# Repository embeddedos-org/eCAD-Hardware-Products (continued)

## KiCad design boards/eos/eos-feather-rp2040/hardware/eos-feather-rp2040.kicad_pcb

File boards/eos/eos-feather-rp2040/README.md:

# EoS Feather RP2040

An original RP2040 board in the Feather form factor, 50.8 × 22.86 mm, four layers.
Designed by Kartikeydheer Srivastava.
All rights reserved: not open source, and not under this repository's MIT licence.
Anyone may view it, clone this repository and run its tests; anything more needs
Kartikeydheer Srivastava's written permission (kartikeydheer@gmail.com). EmbeddedOS (EoS) Research Foundation has a limited, revocable
permission. See [LICENSE.txt](LICENSE.txt) and [the licence summary](../README.md#licence).

A board for the same job as Adafruit's Feather RP2040 (product 4884); an original design, not a
copy: no design file of the vendor's was used (no schematic, layout, CAD, Gerber or BOM). The
outline, hole and header positions come from Adafruit's
[Feather Specification](https://learn.adafruit.com/adafruit-feather/feather-specification) (its
text and dimension drawing), and the signal on each header pin, the user button's GPIO and the
battery polarity from Adafruit's published
[Feather RP2040 pinout](https://learn.adafruit.com/adafruit-feather-rp2040-pico/pinouts) and
its pinout diagram. "Feather" is used only to say what the board fits; it is not an Adafruit
product.

| | |
|---|---|
|  |  |

FeatherWings, and CircuitPython or Arduino code written for the Feather RP2040's pinout, find the
same signals on the same pins. The flash is 16 MB, not 8 MB: firmware built for the Feather
RP2040 runs from its first 8 MB.

## What is on it

| Block | Parts, values and source |
|---|---|
| Outline, holes, headers | 0.9 × 2.0 in with 0.1 in holes at each corner, their centres 0.1 in from each edge. A 16-pin strip along the bottom edge centred 1.0 in from the left edge, a 12-pin strip along the top edge 1.2 in from the left, 0.8 in apart; pin order from the USB end. Source: Adafruit [Feather Specification](https://learn.adafruit.com/adafruit-feather/feather-specification) (text and dimension drawing), as EoS Motion Wing uses it. Holes: KiCad's 2.5 mm unplated hole, the nearest stock size to 0.1 in; corner radius 2.54 mm, concentric with the holes (the spec gives none). Male headers on the back (Würth 61301611121, 61301211121): pins point down, for a breadboard or a Feather socket. |
| MCU | Raspberry Pi RP2040, QFN-56 7 × 7 mm; its single ground is the centre pad (RP2040 datasheet Table 1), which has a 2 × 2 array of vias into the ground plane. 100 nF at each IOVDD and DVDD pin and at USB_VDD and ADC_AVDD (datasheet 2.9.1–2.9.5); 1 µF at VREG_VIN and at VREG_VOUT, which feeds the DVDD pins (datasheet 2.10.1; [Hardware design with RP2040](https://datasheets.raspberrypi.com/rp2040/hardware-design-with-rp2040.pdf) 2.1.3); TESTEN to ground (Table 1). [RP2040 datasheet](https://datasheets.raspberrypi.com/rp2040/rp2040-datasheet.pdf), build 2025-02-20. |
| Crystal | Abracon ABM8-272-T3, 12 MHz, CL 10 pF, ESR 50 Ω, the crystal Raspberry Pi recommends; 15 pF C0G load capacitors and 1 kΩ in series with XOUT, tuned for IOVDD = 3.3 V (Hardware design with RP2040, 2.3 and Table 1). |
| Flash | Winbond W25Q128JVPIQ, 16 MB QSPI, WSON-8 6 × 5 mm: the guide's W25Q128JV (2.2) in its smaller package. 100 nF (C22) beside it, joined to VCC only through the 3.3 V plane (see [Layout](#layout)). Its exposed pad is left unconnected, with no via under it, as the [W25Q128JV data sheet](https://www.winbond.com/resource-files/w25q128jv%20revf%2003272018%20plus.pdf) Rev. F (section 10.3) asks. |
| BOOTSEL | 1 kΩ from QSPI_SS to the BOOT button, so QSPI_SS can over-drive the button when the chip boots; the 10 kΩ QSPI_SS pull-up (R7) is drawn but not fitted, as the guide does for this flash (2.2). |
| USB | HRO TYPE-C-31-M-12 as a 5 V sink: 5.1 kΩ Rd on CC1 and CC2 ([USB Type-C specification](https://www.usb.org/usb-type-cr-cable-and-connector-specification)). Littelfuse SP0503BAHTG on D+, D− and VBUS: diodes to ground only ([SP05xxBA data sheet](https://www.littelfuse.com/~/media/electronics/datasheets/tvs_diode_arrays/littelfuse_tvs_diode_array_sp05_datasheet.pdf.pdf)). 27 Ω in series with USB_DP and USB_DM, at the chip (RP2040 datasheet Table 1; guide 2.4.1). Littelfuse 0805L050WR polyfuse, 0.50 A hold, 1.00 A trip, 6 V, R1max 0.85 Ω (0805L data sheet, revised 10/29/21). |
| LiPo charger | Microchip MCP73831T-2ACI/OT, 4.20 V. R10 = 4.7 kΩ sets 1000 V / 4.7 kΩ = 213 mA (equation 5-1), inside the Feather spec's 100–500 mA. 10 µF on VDD and on VBAT, where the data sheet asks for at least 4.7 µF (sections 3.1, 3.2, 6.1.1.4). Yellow CHG LED from VBUS through 1 kΩ into STAT: lit while charging. [MCP73831 data sheet](https://ww1.microchip.com/downloads/aemDocuments/documents/APID/ProductDocuments/DataSheets/MCP73831-Family-Data-Sheet-DS20001984H.pdf) DS20001984H. |
| Battery and power path | JST PH 2-pin (S2B-PH-SM4-TB), the connector the Feather spec requires, polarity as Adafruit's cells (see [Battery polarity](#battery-polarity)). Load sharing as Microchip [AN1149](https://ww1.microchip.com/downloads/en/AppNotes/01149c.pdf) (DS01149C) Figures 5–7: an AOS AO3401A P-MOSFET from the battery to the system rail, its gate on USB power with a pull-down, and a Nexperia PMEG6010CEH Schottky from USB to the system rail. With USB present the MOSFET is off and USB runs the board while the charger charges the battery; without USB the pull-down turns it on. AO3401A Rev 3.1: RDS(on) ≤ 85 mΩ at VGS = −2.5 V. PMEG6010CEH v.4: VF ≤ 530 mV at 500 mA. The pull-down is 10 kΩ, not AN1149's 100 kΩ: see [Gate pull-down](#gate-pull-down). The battery line passes a 1 mm test pad, TP1, in the top-right corner. |
| 3.3 V | Diodes AP2112K-3.3TRG1, 600 mA, the regulator the Feather spec names; dropout ≤ 400 mV at 600 mA; stable with 1.0 µF ceramic capacitors (X5R/X7R); 10 µF X5R fitted at input and output. The Feather EN pin pulls its EN low; 100 kΩ to the system rail holds it high otherwise (EN high above 1.5 V; 3 MΩ internal pull-down). [AP2112 data sheet](https://www.diodes.com/assets/Datasheets/AP2112.pdf) DS39724 Rev. 2-2. |
| Buttons | RESET (RUN, which has an internal pull-up: RP2040 datasheet Table 619), BOOT and USER, Omron B3U-1000P (A162-E1-07), along the bottom right: RST, USR, BOOT from left to right. USER is on GPIO4, where Adafruit's pinout puts the Feather RP2040's user-readable button; turn on GPIO4's internal pull-up in firmware (the pins reset with pull-downs, datasheet Table 615). |
| LEDs | Red user LED on D13 (GPIO13), Kingbright APTD1608LSURCK through 1 kΩ: 1.55 mA at VF 1.75 V (DSAO7433), under the pin's 4 mA default drive. Yellow CHG LED, APTD1608LSYCK (DSAO7434). The spec asks for the user LED above the USB connector and suggests the CHG LED below it; both are there. |
| SWD | Raspberry Pi 3-pin debug connector, JST SH BM03B-SRSS-TB: 1 SWCLK, 2 GND, 3 SWDIO ([RP-003139-SP-4](https://datasheets.raspberrypi.com/debug/debug-connector-specification.pdf)), marked SWD. It takes a Raspberry Pi Debug Probe's cable. The specification recommends 100 Ω in series at the target's pins "unless the platform is very low cost and/or space constrained"; there is no room for them beside the RP2040's pins 20–26 (XIN, XOUT, DVDD, SWCLK, SWDIO and RUN at 0.4 mm pitch, with R5 and C20 in front of them), so they are left out. |
| STEMMA QT / Qwiic | JST SH SM04B-SRSS-TB on SDA/SCL (GPIO2/GPIO3, I2C1), 1 GND, 2 3.3 V, 3 SDA, 4 SCL ([STEMMA QT technical specs](https://learn.adafruit.com/introducing-adafruit-stemma-qt/technical-specs), the Qwiic convention). No pull-ups on the board: the spec puts them on the I2C devices and on the wings. |

### Feather pins

| Pin | Header | Signal | | Pin | Header | Signal |
|---|---|---|---|---|---|---|
| RST | 16-pin, 1 | RUN | | BAT | 12-pin, 1 | battery + |
| 3V | 16-pin, 2 | 3.3 V | | EN | 12-pin, 2 | regulator enable |
| 3V | 16-pin, 3 | 3.3 V (AREF in the spec; see below) | | USB | 12-pin, 3 | USB 5 V, after the polyfuse |
| GND | 16-pin, 4 | ground | | D13 | 12-pin, 4 | GPIO13, red LED |
| A0–A3 | 16-pin, 5–8 | GPIO26–GPIO29 (ADC0–ADC3) | | D12, D11, D10, D9 | 12-pin, 5–8 | GPIO12, GPIO11, GPIO10, GPIO9 |
| D24, D25 | 16-pin, 9–10 | GPIO24, GPIO25 | | D6, D5 | 12-pin, 9–10 | GPIO8, GPIO7 |
| SCK, MO, MI | 16-pin, 11–13 | GPIO18, GPIO19, GPIO20 (SPI0) | | SCL, SDA | 12-pin, 11–12 | GPIO3, GPIO2 (I2C1), and the STEMMA QT |
| RX, TX | 16-pin, 14–15 | GPIO1, GPIO0 (UART0) | | | | |
| D4 | 16-pin, 16 | GPIO6 | | | | |

GPIO4 is the USER button. GPIO5, GPIO14–17 and GPIO21–23 are not connected. The spec's AREF
position (16-pin, 3) carries 3.3 V, as on Adafruit's pinout: the RP2040 has no separate ADC
reference pin, and the spec says to leave AREF unconnected on such a chip, so a wing that drives
an analog reference into that pin would meet this board's 3.3 V rail.

### Gate pull-down

On battery, D1 is reverse-biased by the system rail and its leakage flows into Q1's gate node,
whose only path to ground is the pull-down. The gate rises by the leakage times the pull-down.
With AN1149's 100 kΩ and a very-low-VF Schottky (onsemi's MBR120VL is allowed 0.6 mA at 25 °C),
the gate could reach the system rail and turn Q1 off. PMEG6010CEH (v.4) leaks 0.8 µA typical at
5 V and at most 50 µA at 60 V (25 °C); its Fig. 2 shows about 65 µA at 5 V and 85 °C (typical;
the data sheet gives no maximum above 25 °C). Through 10 kΩ that lifts the gate at most 0.5 V at
25 °C and about 0.65 V at 85 °C, so VGS stays below −2.3 V down to a 3.0 V cell, past the
AO3401A's −1.3 V maximum threshold. With USB present the pull-down takes 0.5 mA.

### Battery polarity

Adafruit's pinout diagram marks the battery connector: − toward the USB end and + away from it,
on a connector that faces the 12-pin edge. Looking into that connector from outside the board,
top side up, + is on the left. This board's connector faces the right-hand edge and keeps that
convention: looking into it, + (J4 pin 1) is on the left, toward the 16-pin edge. The marks
+ and − are on the silkscreen beside it. Cells from other makers may be wired the other way
round; check a cell with a meter before plugging it in.

## Not on this board

- **NeoPixel.** The Feather RP2040 has an RGB NeoPixel on GPIO16; this board has none, and
  GPIO16 is not connected.
- **The 2 × 5 1.27 mm SWD footprint and the bottom SWD pads.** The Raspberry Pi 3-pin connector
  replaces them.
- **The battery connector's position.** The Feather spec says the JST PH "must" be 0.425 in
  from the left edge, on the 12-pin edge beside the USB connector. With KiCad's stock footprints,
  the courtyards of the HRO TYPE-C-31-M-12 (10.6 mm wide, extended by its rear shell tabs) and of
  the S2B-PH-SM4-TB (10.2 mm deep) overlap at that spot, so the connector is at the right-hand end,
  facing out of it. A USB-C receptacle with a shorter rear, or a mid-mount one, might allow the
  spec position. This is a deviation from a "must" of the spec, awaiting the owner's decision. A
  case or a cable routing that expects the battery lead at the USB end will not fit.
- **USB at the exact centre of the left edge.** The receptacle is centred at y 11.90 mm, 0.47 mm
  below the edge's centre (11.43 mm), where the Feather spec puts USB; an enclosure's plug window
  centred on the edge has 0.47 mm less margin on one side.
- **Header pin labels.** Neither silkscreen labels the header pins; the
  [Feather pins](#feather-pins) table is the key.
- **Battery voltage monitor.** None, as on the Feather RP2040 (Adafruit's power page: no ADC is
  connected to a battery monitor).

## Layout

Measured from the routed board file, `hardware/eos-feather-rp2040.kicad_pcb`.

- **Crystal.** XIN runs 8.4 mm from pin 20 to the crystal and C23; XOUT 2.6 mm from pin 21 to
  R5, then 2.2 mm from R5 to the crystal and C24. All three are on the top layer with no via. On
  the bottom layer under the crystal, C23, C24, R5 and these lines the only track or via of another
  net is one ground via; the bottom ground pour covers the area. Next to the clock tracks, the
  nearest other tracks are those of the chip's neighbouring pins (3.3 V and ground), 0.24 mm away
  at the pad row, and the +1V1 line to C20, 0.55 mm away.
- **USB D+ near the crystal.** On its way from the ESD part to its via under the chip, D+ runs on
  the top layer through the crystal group: 0.17 mm from the crystal's ground pad (Y1.2), 0.18 mm
  from C24's ground pad (C24.2), 0.59 mm from C24's XTAL_OUT pad (C24.1) and 0.88 mm from the
  XTAL_OUT track, edge to edge. It crosses no clock line, and the ground plane (In1) under it there
  is solid. Rev B moves it out of the group (see [Rev B follow-ups](#rev-b-follow-ups)).
- **USB.** From the receptacle through the ESD part to R3 and R4: D+ 36.3 mm with 4 vias (two of
  them join the receptacle's A6 and B6 contacts), D− 35.1 mm with 2 vias, 0.2 mm wide. They are
  not a coupled pair: D+ runs 21.4 mm on the top layer and 14.9 mm on the bottom, D− 7.4 mm on the
  top and 27.7 mm on the bottom. Under the chip both are on the bottom layer, 0.5 to 1.4 mm apart
  centre to centre. From R3 and R4 to pins 47 and 46: 3.9 and 4.1 mm on the top layer.
- **QSPI.** SCLK 4.4 mm, SD0 2.9 mm, SD1 11.5 mm, SD2 9.0 mm, SD3 5.8 mm, all on the top layer
  with no via. SS runs 11.9 mm on the top layer from pin 56 to the flash's CS pad. From there a
  branch goes on to the BOOTSEL resistors right of the flash: 8.21 mm to R6 and 9.45 mm to R7
  (7.61 mm on the top layer, 1.84 mm on the bottom, 2 vias), where Hardware design with RP2040
  (2.2) asks for both resistors close to the flash. Rev B routes it directly.
- **Core supply (+1V1).** Each pin has a top-layer track to its capacitor: VREG_VOUT (pin 45) to
  C11 2.5 mm, DVDD pin 50 to C21 2.3 mm, DVDD pin 23 to C20 3.2 mm. One 0.2 mm line joins them:
  from C11 round the end of the USB D+ line beside R3, then on the bottom layer under the chip to
  C20, with a via down to it from pin 50's track; 32.6 mm of +1V1 track in all, 3 vias.
- **3.3 V decoupling, supply side.** Track length along the centrelines, pad centre to via
  centre. Each 3.3 V pin of the RP2040 has its own via inside the pad ring: 0.86 mm from pins 1,
  10, 22, 33, 42 and 48, 1.46 mm from pins 43 and 49, 2.06 mm from pin 44 (VREG_VIN); pin 43's
  track also passes over pin 42's via. C15 sits 1.2 mm from pin 33 on a direct top-layer track and
  uses pin 33's via. C12, C13, C14 and C16 have a via each (0.73 to 0.74 mm). C10 and C18 share
  one (C18 0.73 mm; C10 1.73 mm, through C18's pad). C17, C19 and C22 share another (C19 0.73 mm,
  C17 2.64 mm, C22 5.36 mm through C17's pad). Capacitor pad to pin pad: C16 1.4 mm (pin 42), C10
  3.3 mm (VREG_VIN, pin 44), C13 4.5 mm (pin 10), C18 5.0 mm (USB_VDD, pin 48), C19 5.1 mm
  (ADC_AVDD, pin 43), C17 6.5 mm (pin 49), C14 7.5 mm (pin 22), C12 8.2 mm (pin 1).
- **Decoupling, ground side.** Copper path from the pad's edge to the nearest ground via: C21's
  ground pad (DVDD pin 50) has the longest of any decoupling capacitor, 3.38 mm of top copper, to
  a via that C17 (1.93 mm) and C22 (0.33 mm) also use.
- **Flash decoupling.** C22, the flash's 100 nF, has no track to the flash's VCC pin (U2.8): it
  is turned with its ground pad between U2.8 and its 3.3 V pad. It reaches U2.8 only through the
  3.3 V plane: from C22's 3.3 V pad, 4.55 mm of copper (5.36 mm along the track centrelines) to
  the via it shares with C17 and C19, and that via is 6.73 mm from U2.8's own via. Hardware
  design with RP2040 (Figure 11) puts the 100 nF at the flash's VCC. Rev B turns C22 and routes
  it to U2.8, and moves C12, C14 and C17 nearer their pins.
- **Lines to the bottom right.** GPIO0 (TX), GPIO1 (RX), GPIO6 (D4) and GPIO4 (user button)
  leave the chip's top edge and change to the bottom layer above it. They run under the flash to
  the 16-pin strip and the button: 22.2, 22.3, 26.7 and 20.1 mm, with one or two vias each.
- **Battery line.** VBAT, 0.3 mm wide (0.225 mm where it enters the charger's pin), runs from
  J4 past TP1 and along the top edge, under the 12-pin strip, to the BAT pin and on to the
  charger: 63.3 mm with 3 vias.
- **Ground.** Ground is poured on both outer layers, with 39 ground vias. Every fragment of the
  outer-layer ground pours contains a ground via or a plated-through ground pin.

## Build results

The numbers below are from `build-report.json` and `drc.json` in this folder.

| Check | Result |
|---|---|
| Schematic ERC | 0 violations |
| DRC errors | 0 |
| Unconnected items | 0 |
| Schematic ↔ board parity | 0 differences |
| DRC warnings | 7: silkscreen within the board-edge clearance: the front outline of J1 (USB-C) at the left edge (2), and the back outlines of J2 (Feather 16-pin) and J3 (Feather 12-pin) at the bottom and top edges (2 and 3) |

## Fabrication

Four layers, 1.6 mm FR-4: signal, ground plane, 3.3 V plane, signal, with ground poured on both
outer layers. Measured from the board file:

- **Tracks:** 0.127 mm for signals; 0.2 mm for USB and +1V1, which enter the RP2040's
  0.4 mm-pitch pads; 0.2 and 0.3 mm for +3V3; 0.3 mm for VBUS, the battery and the system rail;
  ground tracks 0.127, 0.2 and 0.3 mm. Narrower where a track enters a fine-pitch pad: 0.095 mm
  on the USB-C receptacle's CC contacts, 0.225 mm on VBUS and VBAT at the receptacle and the
  charger, and one 0.15 mm segment on +3V3.
- **Clearance:** 0.127 mm; 0.15 mm around the USB, supply and power lines (their net classes).
- **Vias:** 0.45 mm with a 0.2 mm drill (109 vias).
- **Smallest drill:** 0.2 mm, in the vias.
- **Plated slots:** the USB-C receptacle's four shell holes are plated oval slots, 0.6 × 1.2 mm and
  0.6 × 1.7 mm (two of each): tell the fab the board has plated slots. Its two 0.65 mm peg holes
  are unplated.

The four vias in the RP2040's centre pad sit in its paste openings: order them filled and capped
(or plugged), so solder does not wick down them.

## What has not been done

- **No board has been made or tested.** These are design files that pass KiCad's electrical and
  design rule checks; no hardware has been built, powered, charged from or flashed.
- **No signal-integrity, thermal or charging test.** USB, QSPI and the crystal were not simulated
  or measured. The charger's thermal regulation and the AP2112K's temperature at full load were
  not measured.
- **Regulator heat.** The AP2112K's SOT-25 package is rated 184 °C/W (no heatsink). From USB the
  system rail is about 4.3–4.5 V, so 500 mA from the 3.3 V rail dissipates about 0.55 W, a rise of
  about 100 °C: the 500 mA is a peak, not a continuous load.
- **Charger heat.** The MCP73831 (230 °C/W, 4-layer JEDEC board) dissipates about 0.3 W at 213 mA
  from 5 V into a 3.6 V cell. The worst case is at the start of constant-current charging, where
  the cell is at the precondition threshold, 66.5 % of 4.20 V = 2.79 V (DS20001984H, VPTH/VREG):
  (5 − 2.79) V × 0.213 A = about 0.47 W, a rise of about 108 °C, so the charger's thermal
  regulation will cut the current there.
- **USB budget.** The polyfuse holds 0.50 A at 20 °C, and less when warm: 0.40 A at 40 °C, 0.37 A
  at 50 °C and 0.33 A at 60 °C (0805L data sheet, temperature rerating table, 0805L050). The
  charger takes up to 213 mA of it, so while a battery charges the board and its wings should stay
  under about 287 mA at 20 °C (0.50 A − 213 mA) and about 187 mA at 40 °C (0.40 A − 213 mA).
- **Capacitance at USB attach.** USB 2.0 (section 7.2.4.1) allows at most 10 µF across VBUS when
  a device is plugged in. This board has C30 (10 µF) on VBUS directly, behind the polyfuse, C32
  (10 µF) behind D1, and about 12 µF on the 3.3 V rail behind the AP2112K, with no inrush
  limiting. Not measured.
- **Bulk capacitors' DC bias.** C30–C33 are 10 µF 16 V X5R 0805 capacitors with no part number.
  The MCP73831 needs at least 4.7 µF on VDD and on VBAT (DS20001984H sections 3.1, 3.2 and
  6.1.1.4); a typical 16 V 0805 X5R part keeps about 40–60 % of its capacitance at 5 V (Assumed:
  no capacitor data sheet was checked), so that margin is open.
- **3D models.** KiCad 10.0.6 ships none for the HRO TYPE-C-31-M-12 (J1) or the JST
  S2B-PH-SM4-TB (J4), so the STEP file and the renders lack them.
- **Mechanical fit** with Feather cases and stacked FeatherWings has not been tried.

## Rev B follow-ups

- Move USB D+ out of the crystal group (see [Layout](#layout)).
- Turn C22 and route it to the flash's VCC pin; move C12, C14 and C17 nearer pins 1, 22 and 49;
  give C21's ground pad a via of its own.
- Centre the USB-C receptacle on the left edge.
- Route the BOOTSEL/R7 branch directly from the flash's CS pad, close to the flash.
- Name the USB Type-C specification as the source in R1's and R2's Description fields.
- Name a 10 µF part whose DC-bias curve is checked against the MCP73831's 4.7 µF minimum.
- Add header pin labels to the silkscreen.

Awaiting the owner's decision: the battery connector's position (see
[Not on this board](#not-on-this-board)).

## Rebuild

```
python3 tools/eos_boards/build.py eos_feather_rp2040
```

The autorouter (Freerouting) gives a different result on every run, so a rebuild may not pass
the checks first time: builds 9 to 12 of this board each left different connections open. The
files in this folder are from the build that passed.

The design file is [tools/eos_boards/boards/eos_feather_rp2040.py](../../../tools/eos_boards/boards/eos_feather_rp2040.py).

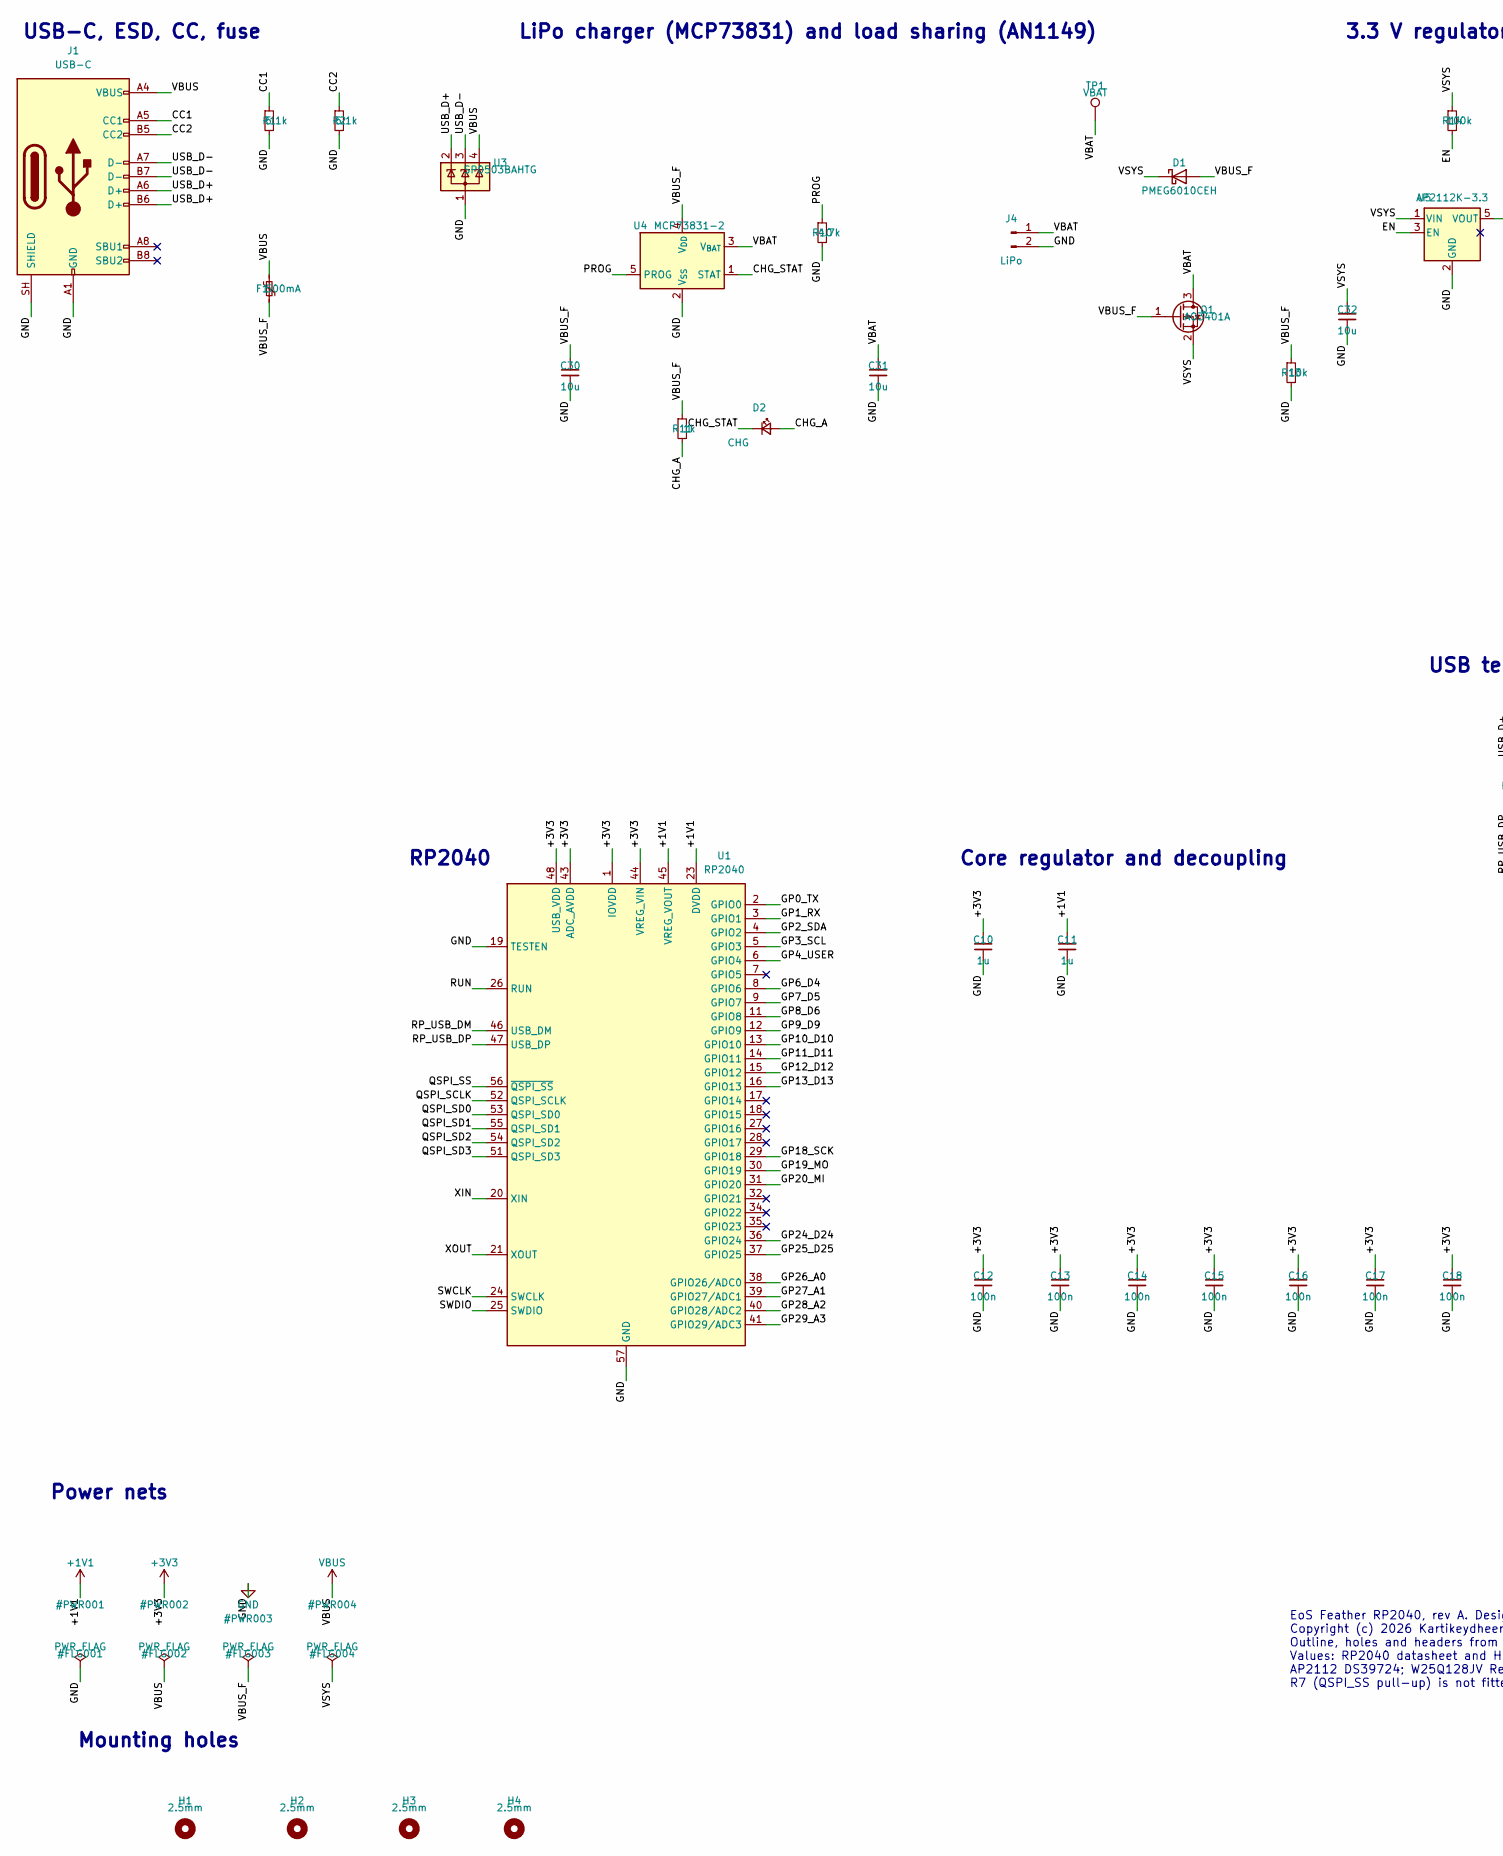
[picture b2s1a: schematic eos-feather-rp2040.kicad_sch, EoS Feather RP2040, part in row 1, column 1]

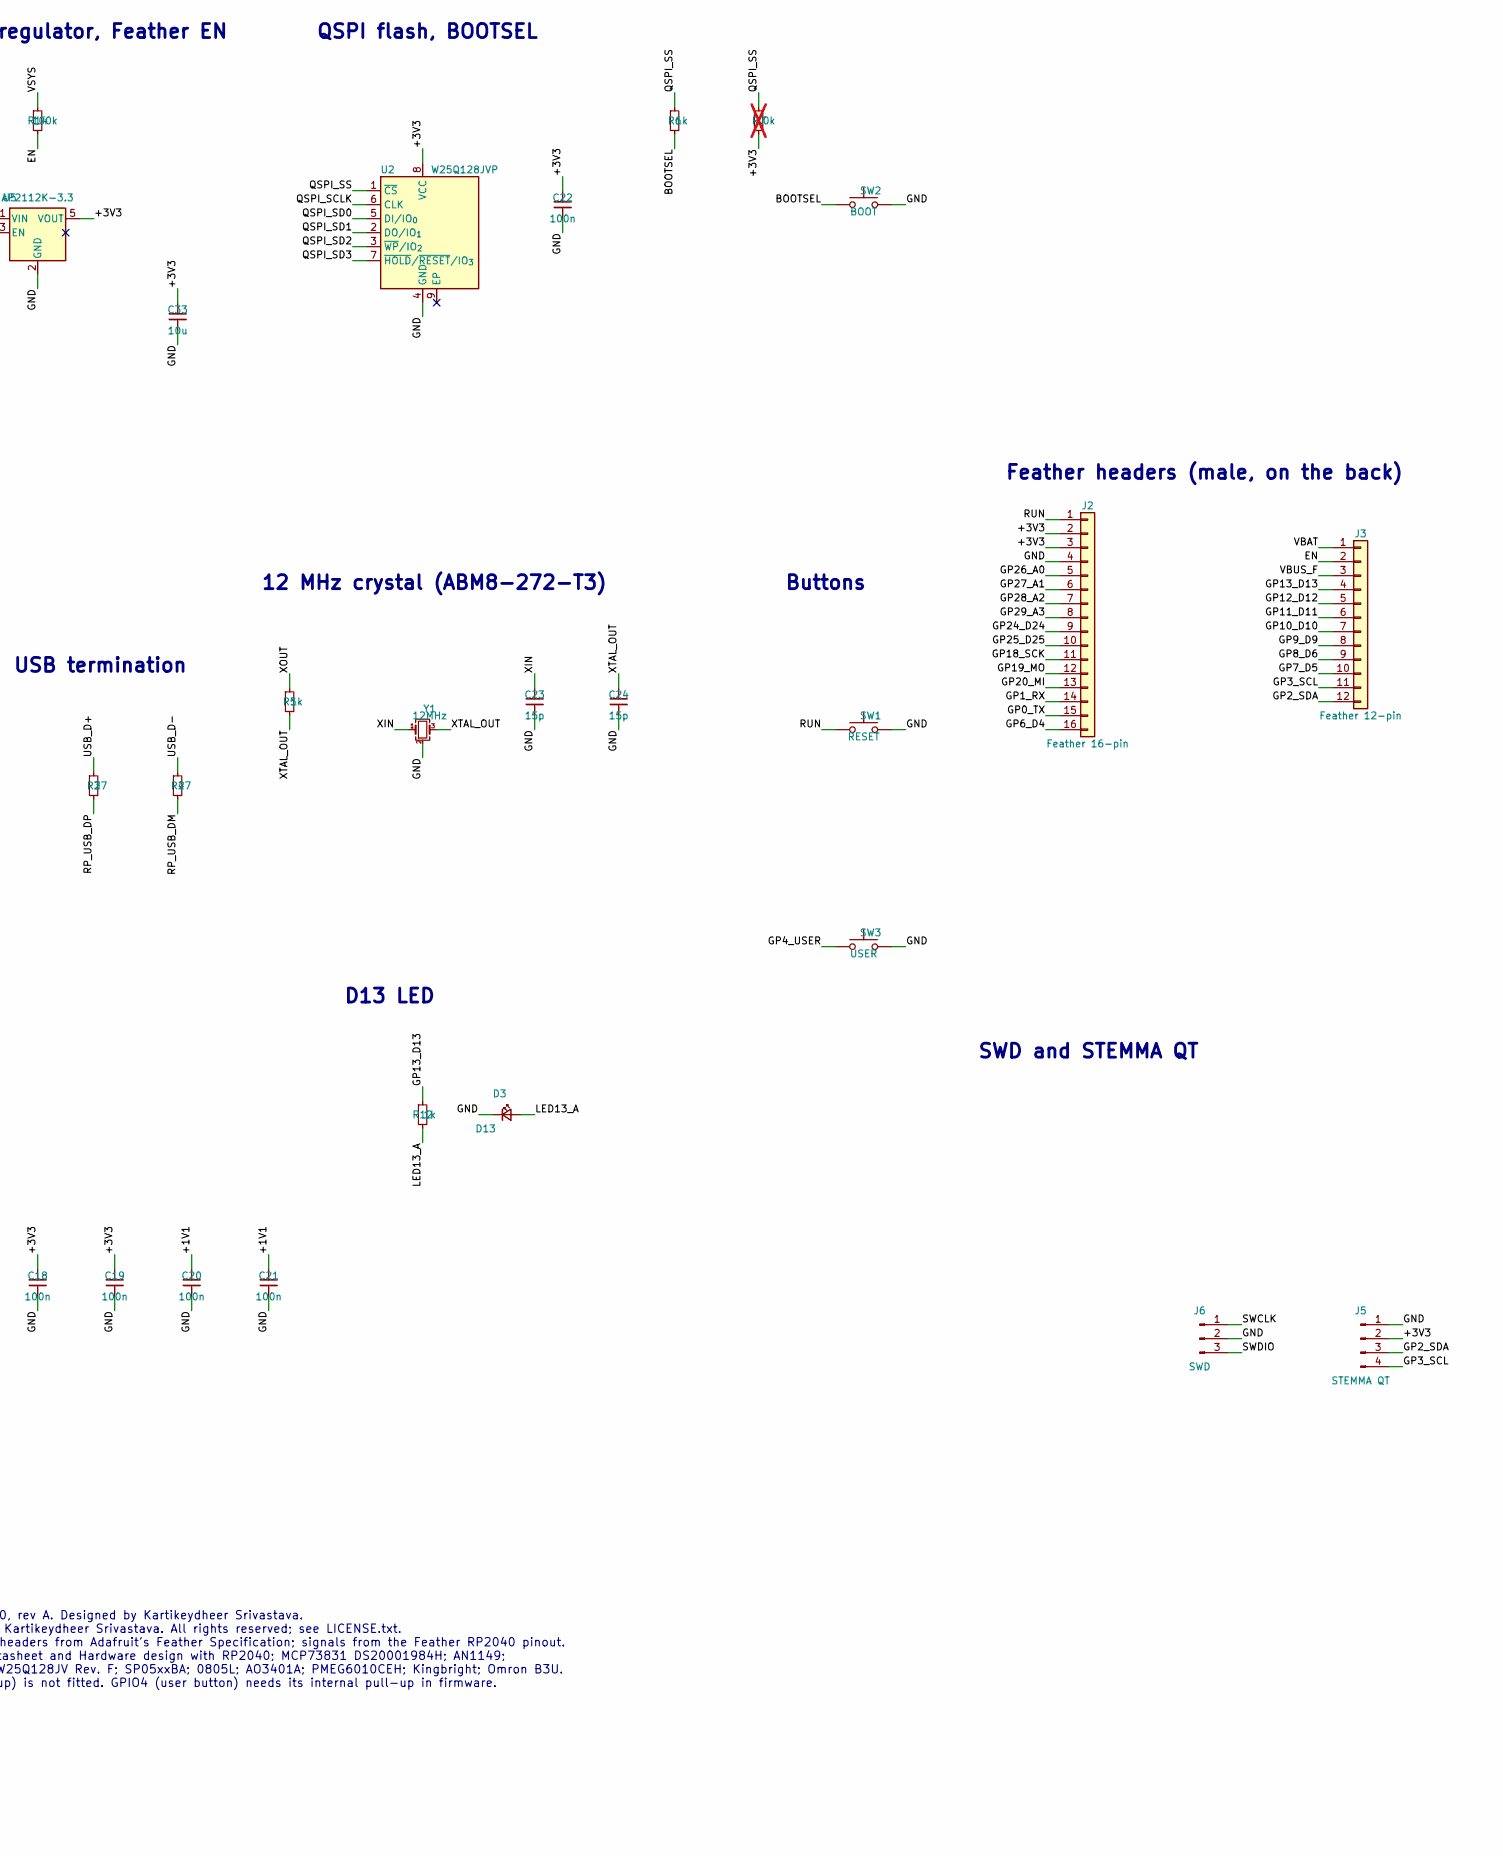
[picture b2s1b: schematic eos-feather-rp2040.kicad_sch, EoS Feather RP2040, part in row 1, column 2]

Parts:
C10, C11: 1u; C_0402_1005Metric
C12, C13, C14, C15, C16, C17, C18, C19, C20, C21, C22: 100n; C_0402_1005Metric
C23, C24: 15p; C_0402_1005Metric
C30, C31, C32, C33: 10u; C_0805_2012Metric
D1: PMEG6010CEH; D_SOD-123F; MPN PMEG6010CEH
D2: CHG; LED_0603_1608Metric; MPN APTD1608LSYCK
D3: D13; LED_0603_1608Metric; MPN APTD1608LSURCK
F1: 500mA; Fuse_0805_2012Metric; MPN 0805L050WR
H1, H2, H3, H4: 2.5mm; MountingHole_2.5mm
J1: USB-C; USB_C_Receptacle_HRO_TYPE-C-31-M-12; MPN TYPE-C-31-M-12
J2: Feather 16-pin; PinHeader_1x16_P2.54mm_Vertical; MPN 61301611121
J3: Feather 12-pin; PinHeader_1x12_P2.54mm_Vertical; MPN 61301211121
J4: LiPo; JST_PH_S2B-PH-SM4-TB_1x02-1MP_P2.00mm_Horizontal; MPN S2B-PH-SM4-TB
J5: STEMMA QT; JST_SH_SM04B-SRSS-TB_1x04-1MP_P1.00mm_Horizontal; MPN SM04B-SRSS-TB
J6: SWD; JST_SH_BM03B-SRSS-TB_1x03-1MP_P1.00mm_Vertical; MPN BM03B-SRSS-TB
Q1: AO3401A; SOT-23; MPN AO3401A
R1, R2: 5.1k; R_0402_1005Metric
R3, R4: 27; R_0402_1005Metric
R5, R6, R11, R12: 1k; R_0402_1005Metric
R7: 10k; R_0402_1005Metric; not fitted
R10: 4.7k; R_0402_1005Metric
R13: 10k; R_0402_1005Metric
R14: 100k; R_0402_1005Metric
SW1: RESET; SW_SPST_B3U-1000P; MPN B3U-1000P
SW2: BOOT; SW_SPST_B3U-1000P; MPN B3U-1000P
SW3: USER; SW_SPST_B3U-1000P; MPN B3U-1000P
TP1: VBAT; TestPoint_Pad_D1.0mm
U1: RP2040; QFN-56-1EP_7x7mm_P0.4mm_EP3.2x3.2mm; MPN RP2040
U2: W25Q128JVP; WSON-8-1EP_6x5mm_P1.27mm_EP3.4x4.3mm; MPN W25Q128JVPIQ
U3: SP0503BAHTG; SOT-143; MPN SP0503BAHTG
U4: MCP73831-2; SOT-23-5; MPN MCP73831T-2ACI/OT
U5: AP2112K-3.3; SOT-23-5; MPN AP2112K-3.3TRG1
Y1: 12MHz; Crystal_SMD_3225-4Pin_3.2x2.5mm; MPN ABM8-272-T3

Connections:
+1V1: C11.1, C20.1, C21.1, U1.23 (DVDD), U1.45 (VREG_VOUT), U1.50 (DVDD)
+3V3: C10.1, C12.1, C13.1, C14.1, C15.1, C16.1, C17.1, C18.1, C19.1, C22.1, C33.1, J2.2, J2.3, J5.2, R7.2, U1.1 (IOVDD), U1.10 (IOVDD), U1.22 (IOVDD), U1.33 (IOVDD), U1.42 (IOVDD), U1.43 (ADC_AVDD), U1.44 (VREG_VIN), U1.48 (USB_VDD), U1.49 (IOVDD), U2.8 (VCC), U5.5 (VOUT)
/BOOTSEL: R6.2, SW2.1
/CC1: J1.A5 (CC1), R1.1
/CC2: J1.B5 (CC2), R2.1
/CHG_A: D2.2 (A), R11.2
/CHG_STAT: D2.1 (K), U4.1 (STAT)
/EN: J3.2, R14.2, U5.3 (EN)
/GP0_TX: J2.15, U1.2 (GPIO0)
/GP1_RX: J2.14, U1.3 (GPIO1)
/GP2_SDA: J3.12, J5.3, U1.4 (GPIO2)
/GP3_SCL: J3.11, J5.4, U1.5 (GPIO3)
/GP4_USER: SW3.1, U1.6 (GPIO4)
/GP6_D4: J2.16, U1.8 (GPIO6)
/GP7_D5: J3.10, U1.9 (GPIO7)
/GP8_D6: J3.9, U1.11 (GPIO8)
/GP9_D9: J3.8, U1.12 (GPIO9)
/GP10_D10: J3.7, U1.13 (GPIO10)
/GP11_D11: J3.6, U1.14 (GPIO11)
/GP12_D12: J3.5, U1.15 (GPIO12)
/GP13_D13: J3.4, R12.1, U1.16 (GPIO13)
/GP18_SCK: J2.11, U1.29 (GPIO18)
/GP19_MO: J2.12, U1.30 (GPIO19)
/GP20_MI: J2.13, U1.31 (GPIO20)
/GP24_D24: J2.9, U1.36 (GPIO24)
/GP25_D25: J2.10, U1.37 (GPIO25)
/GP26_A0: J2.5, U1.38 (GPIO26/ADC0)
/GP27_A1: J2.6, U1.39 (GPIO27/ADC1)
/GP28_A2: J2.7, U1.40 (GPIO28/ADC2)
/GP29_A3: J2.8, U1.41 (GPIO29/ADC3)
/LED13_A: D3.2 (A), R12.2
/PROG: R10.1, U4.5 (PROG)
/QSPI_SCLK: U1.52 (QSPI_SCLK), U2.6 (CLK)
/QSPI_SD0: U1.53 (QSPI_SD0), U2.5 (DI/IO_{0})
/QSPI_SD1: U1.55 (QSPI_SD1), U2.2 (DO/IO_{1})
/QSPI_SD2: U1.54 (QSPI_SD2), U2.3 (~WP/IO_{2})
/QSPI_SD3: U1.51 (QSPI_SD3), U2.7 (~HOLD/~RESET/IO_{3})
/QSPI_SS: R6.1, R7.1, U1.56 (~QSPI_SS), U2.1 (~CS)
/RP_USB_DM: R4.2, U1.46 (USB_DM)
/RP_USB_DP: R3.2, U1.47 (USB_DP)
/RUN: J2.1, SW1.1, U1.26 (RUN)
/SWCLK: J6.1, U1.24 (SWCLK)
/SWDIO: J6.3, U1.25 (SWDIO)
/USB_D+: J1.A6 (D+), J1.B6 (D+), R3.1, U3.2 (K)
/USB_D-: J1.A7 (D-), J1.B7 (D-), R4.1, U3.3 (K)
/VBAT: C31.1, J3.1, J4.1, Q1.3 (D), TP1.1, U4.3 (V_{BAT})
/VBUS_F: C30.1, D1.2 (A), F1.2, J3.3, Q1.1 (G), R11.1, R13.1, U4.4 (V_{DD})
/VSYS: C32.1, D1.1 (K), Q1.2 (S), R14.1, U5.1 (VIN)
/XIN: C23.1, U1.20 (XIN), Y1.1
/XOUT: R5.1, U1.21 (XOUT)
/XTAL_OUT: C24.1, R5.2, Y1.3
GND: C10.2, C11.2, C12.2, C13.2, C14.2, C15.2, C16.2, C17.2, C18.2, C19.2, C20.2, C21.2, C22.2, C23.2, C24.2, C30.2, C31.2, C32.2, C33.2, D3.1 (K), J1.A1 (GND), J1.A12 (GND), J1.B1 (GND), J1.B12 (GND), J1.SH (SHIELD), J2.4, J4.2, J5.1, J6.2, R1.2, R2.2, R10.2, R13.2, SW1.2, SW2.2, SW3.2, U1.19 (TESTEN), U1.57 (GND), U2.4 (GND), U3.1 (A), U4.2 (V_{SS}), U5.2 (GND), Y1.2 (G), Y1.4 (G)
VBUS: F1.1, J1.A4 (VBUS), J1.A9 (VBUS), J1.B4 (VBUS), J1.B9 (VBUS), U3.4 (K)

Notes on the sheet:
USB-C, ESD, CC, fuse
LiPo charger (MCP73831) and load sharing (AN1149)
3.3 V regulator, Feather EN
RP2040
Core regulator and decoupling
USB termination
QSPI flash, BOOTSEL
12 MHz crystal (ABM8-272-T3)
Buttons
D13 LED
SWD and STEMMA QT
Feather headers (male, on the back)
Mounting holes
Power nets
EoS Feather RP2040, rev A. Designed by Kartikeydheer Srivastava. Copyright (c) 2026 Kartikeydheer Srivastava. All rights reserved; see LICENSE.txt. Outline, holes and headers from Adafruit's Feather Specification; signals from the Feather RP2040 pinout. Values: RP2040 datasheet and Hardware design 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

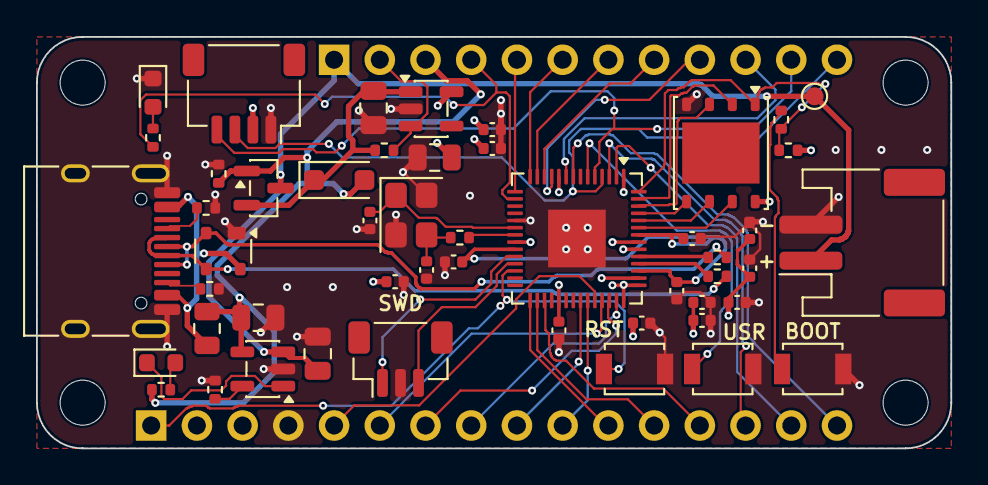
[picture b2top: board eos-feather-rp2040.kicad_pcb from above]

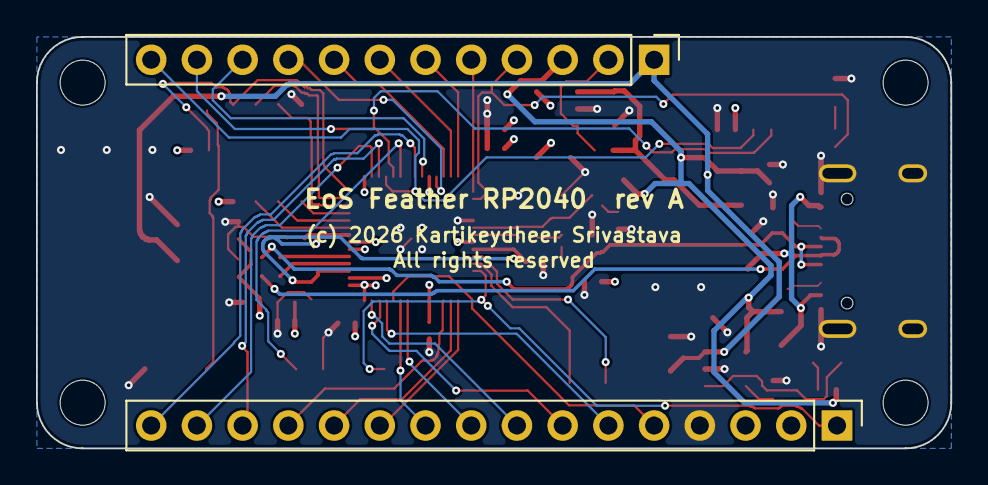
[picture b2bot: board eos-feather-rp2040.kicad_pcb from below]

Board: 4 copper layers, 50.8 x 22.9 mm, 56 parts (2 on the bottom side), 53 nets.
